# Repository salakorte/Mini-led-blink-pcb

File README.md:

# Mini-led-blink-pcb
Pequeña pcb que hace parpadear led mediante componentes diseñado en kiakad y pcb fabricada con acido de forma manual

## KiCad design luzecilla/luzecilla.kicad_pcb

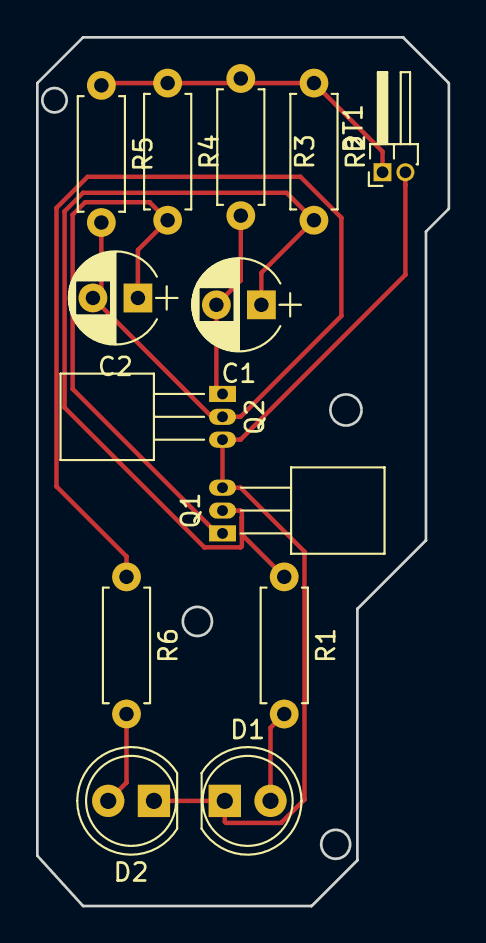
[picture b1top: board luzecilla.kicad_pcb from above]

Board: 2 copper layers, 22.9 x 48.3 mm, 13 parts (0 on the bottom side), 8 nets.

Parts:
BT1: 5v; Pin_Header_Angled_1x02_Pitch1.27mm
C1, C2: 10uF; CP_Radial_D5.0mm_P2.50mm
D1, D2: LED_rojo; LED_D5.0mm
Q1, Q2: BC549B; TO-92_Horizontal1_Inline_Narrow_Oval
R1, R6: 330; R_Axial_DIN0207_L6.3mm_D2.5mm_P7.62mm_Horizontal
R2, R5: 1k; R_Axial_DIN0207_L6.3mm_D2.5mm_P7.62mm_Horizontal
R3, R4: 100k; R_Axial_DIN0207_L6.3mm_D2.5mm_P7.62mm_Horizontal

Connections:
GND: BT1.2, D1.1, D2.1, Q1.3, Q2.3
unnamed: BT1.1, R2.1, R3.1, R4.1, R5.1
unnamed: C1.1, Q1.2, R1.1, R2.2
unnamed: C1.2, Q2.1, R3.2
unnamed: C2.1, Q1.1, R4.2
unnamed: C2.2, Q2.2, R5.2, R6.1
unnamed: D1.2, R1.2
unnamed: D2.2, R6.2
